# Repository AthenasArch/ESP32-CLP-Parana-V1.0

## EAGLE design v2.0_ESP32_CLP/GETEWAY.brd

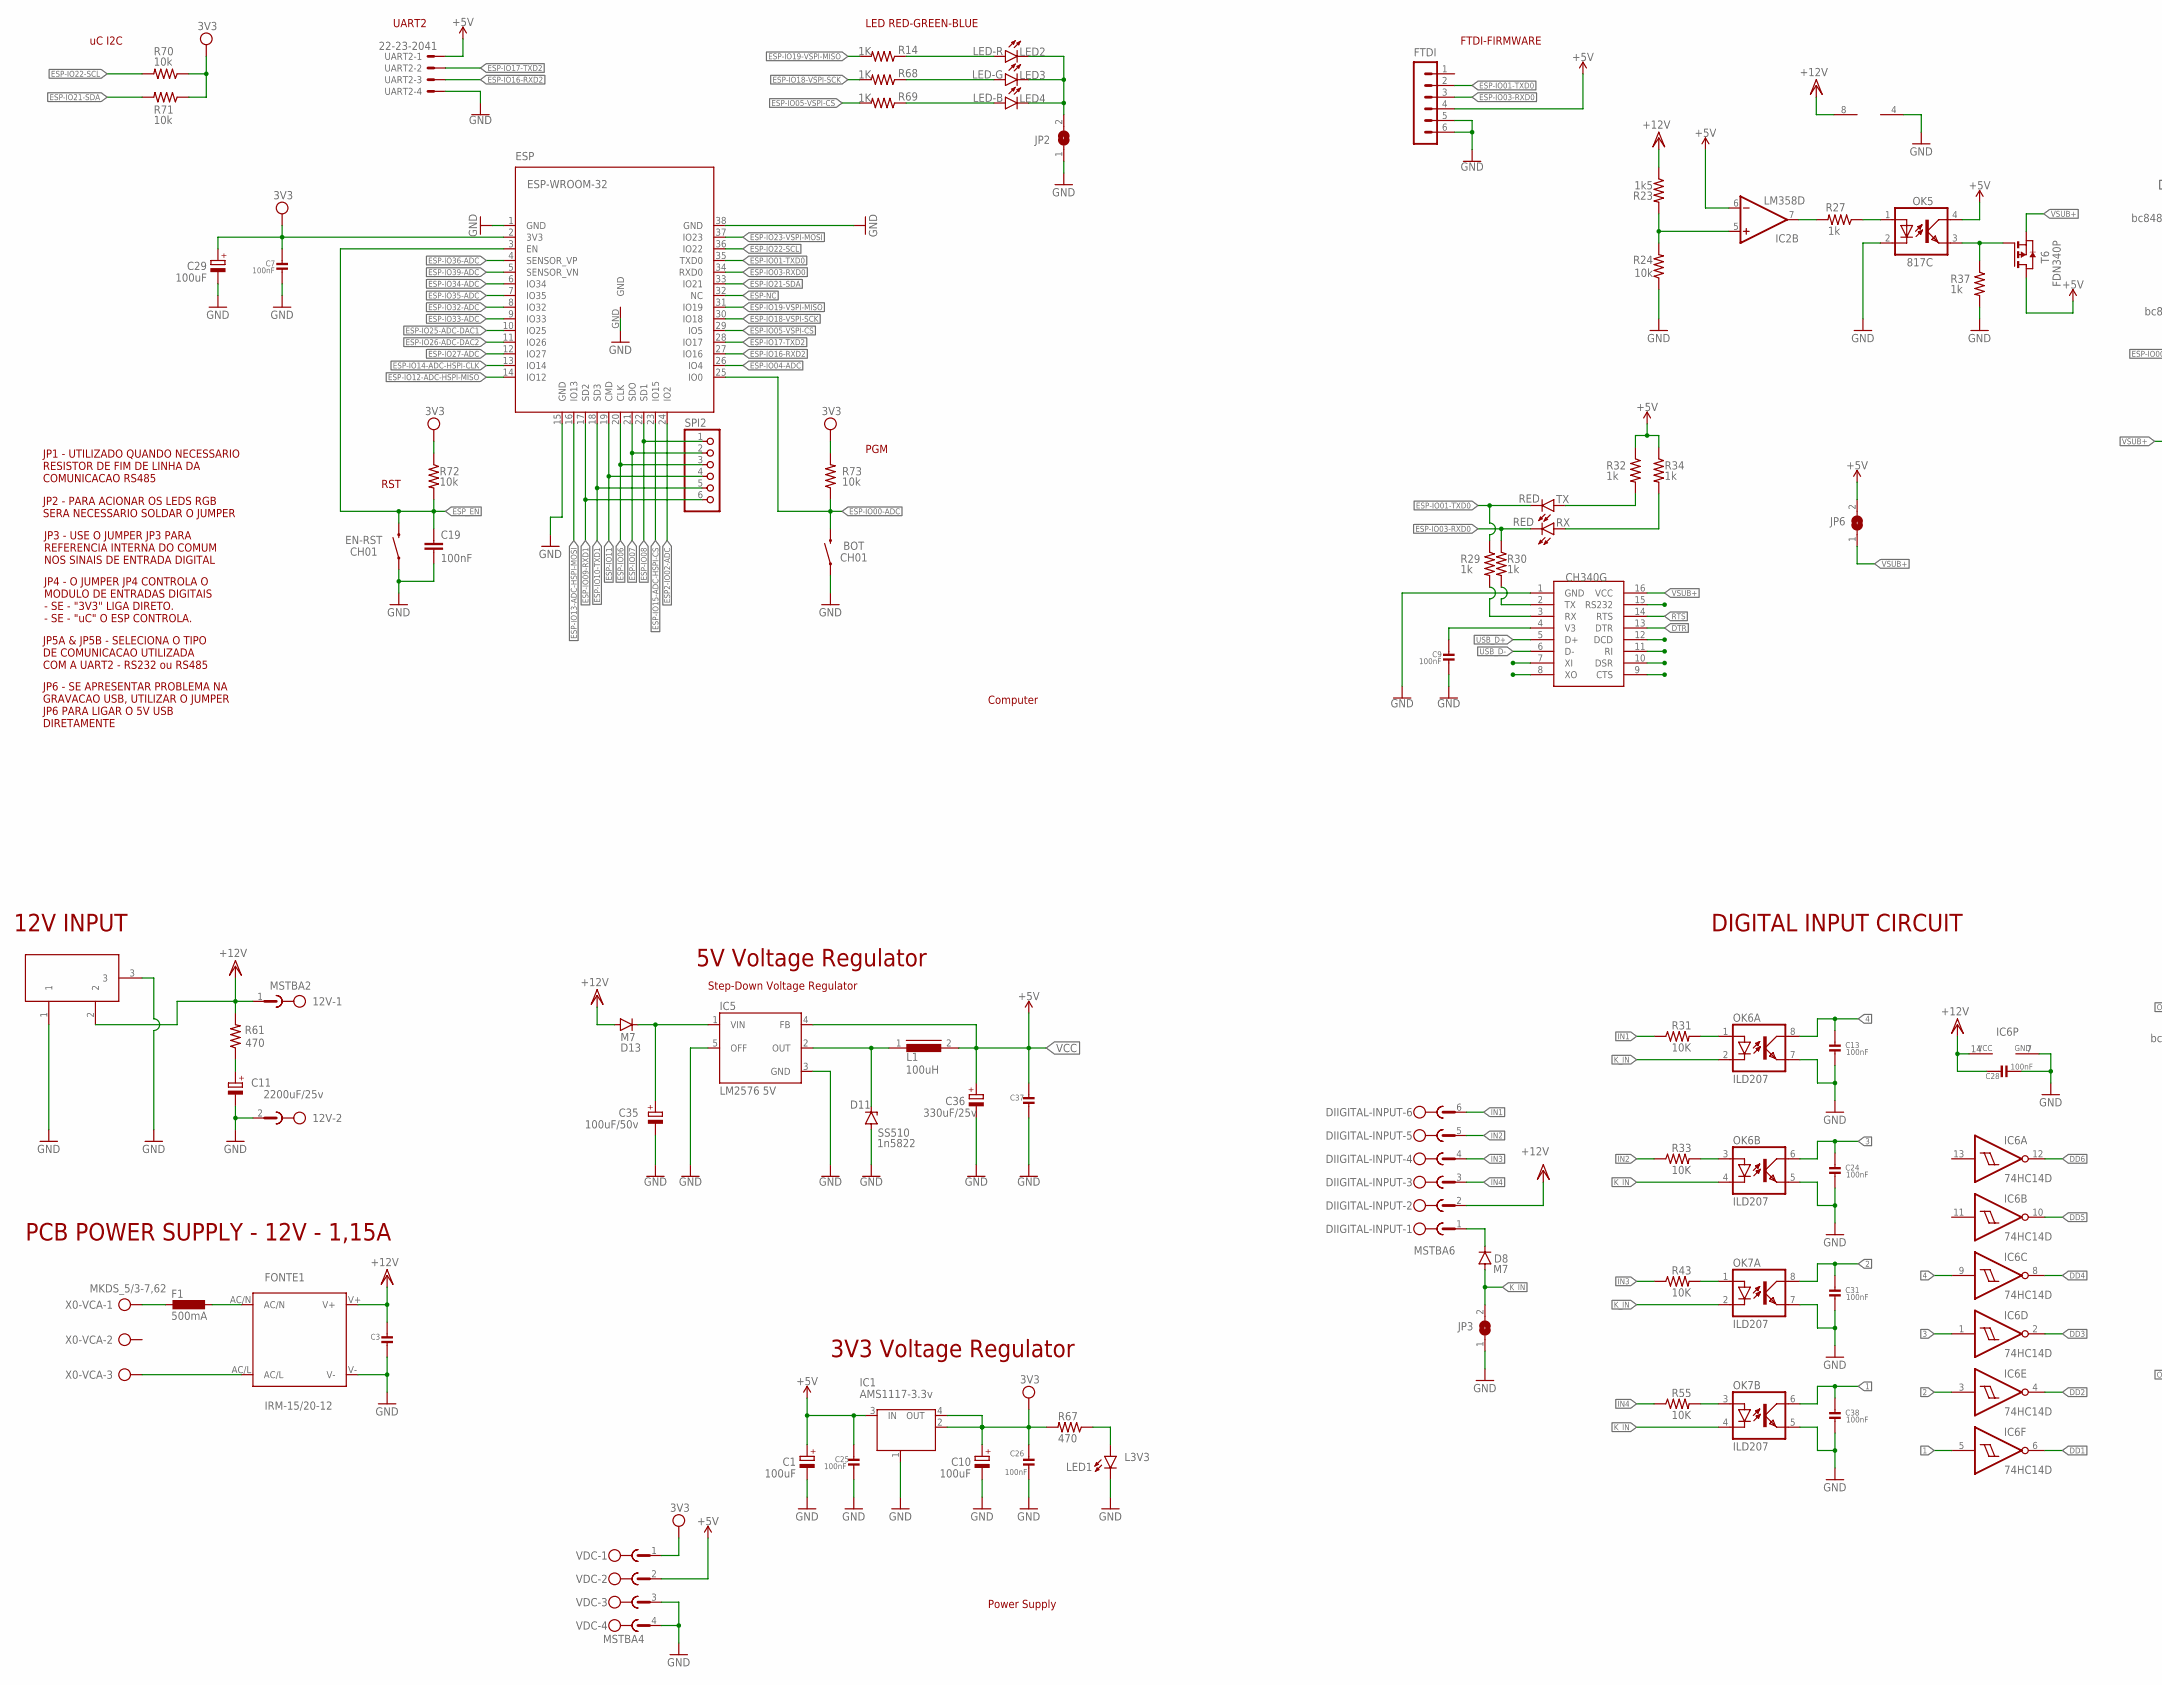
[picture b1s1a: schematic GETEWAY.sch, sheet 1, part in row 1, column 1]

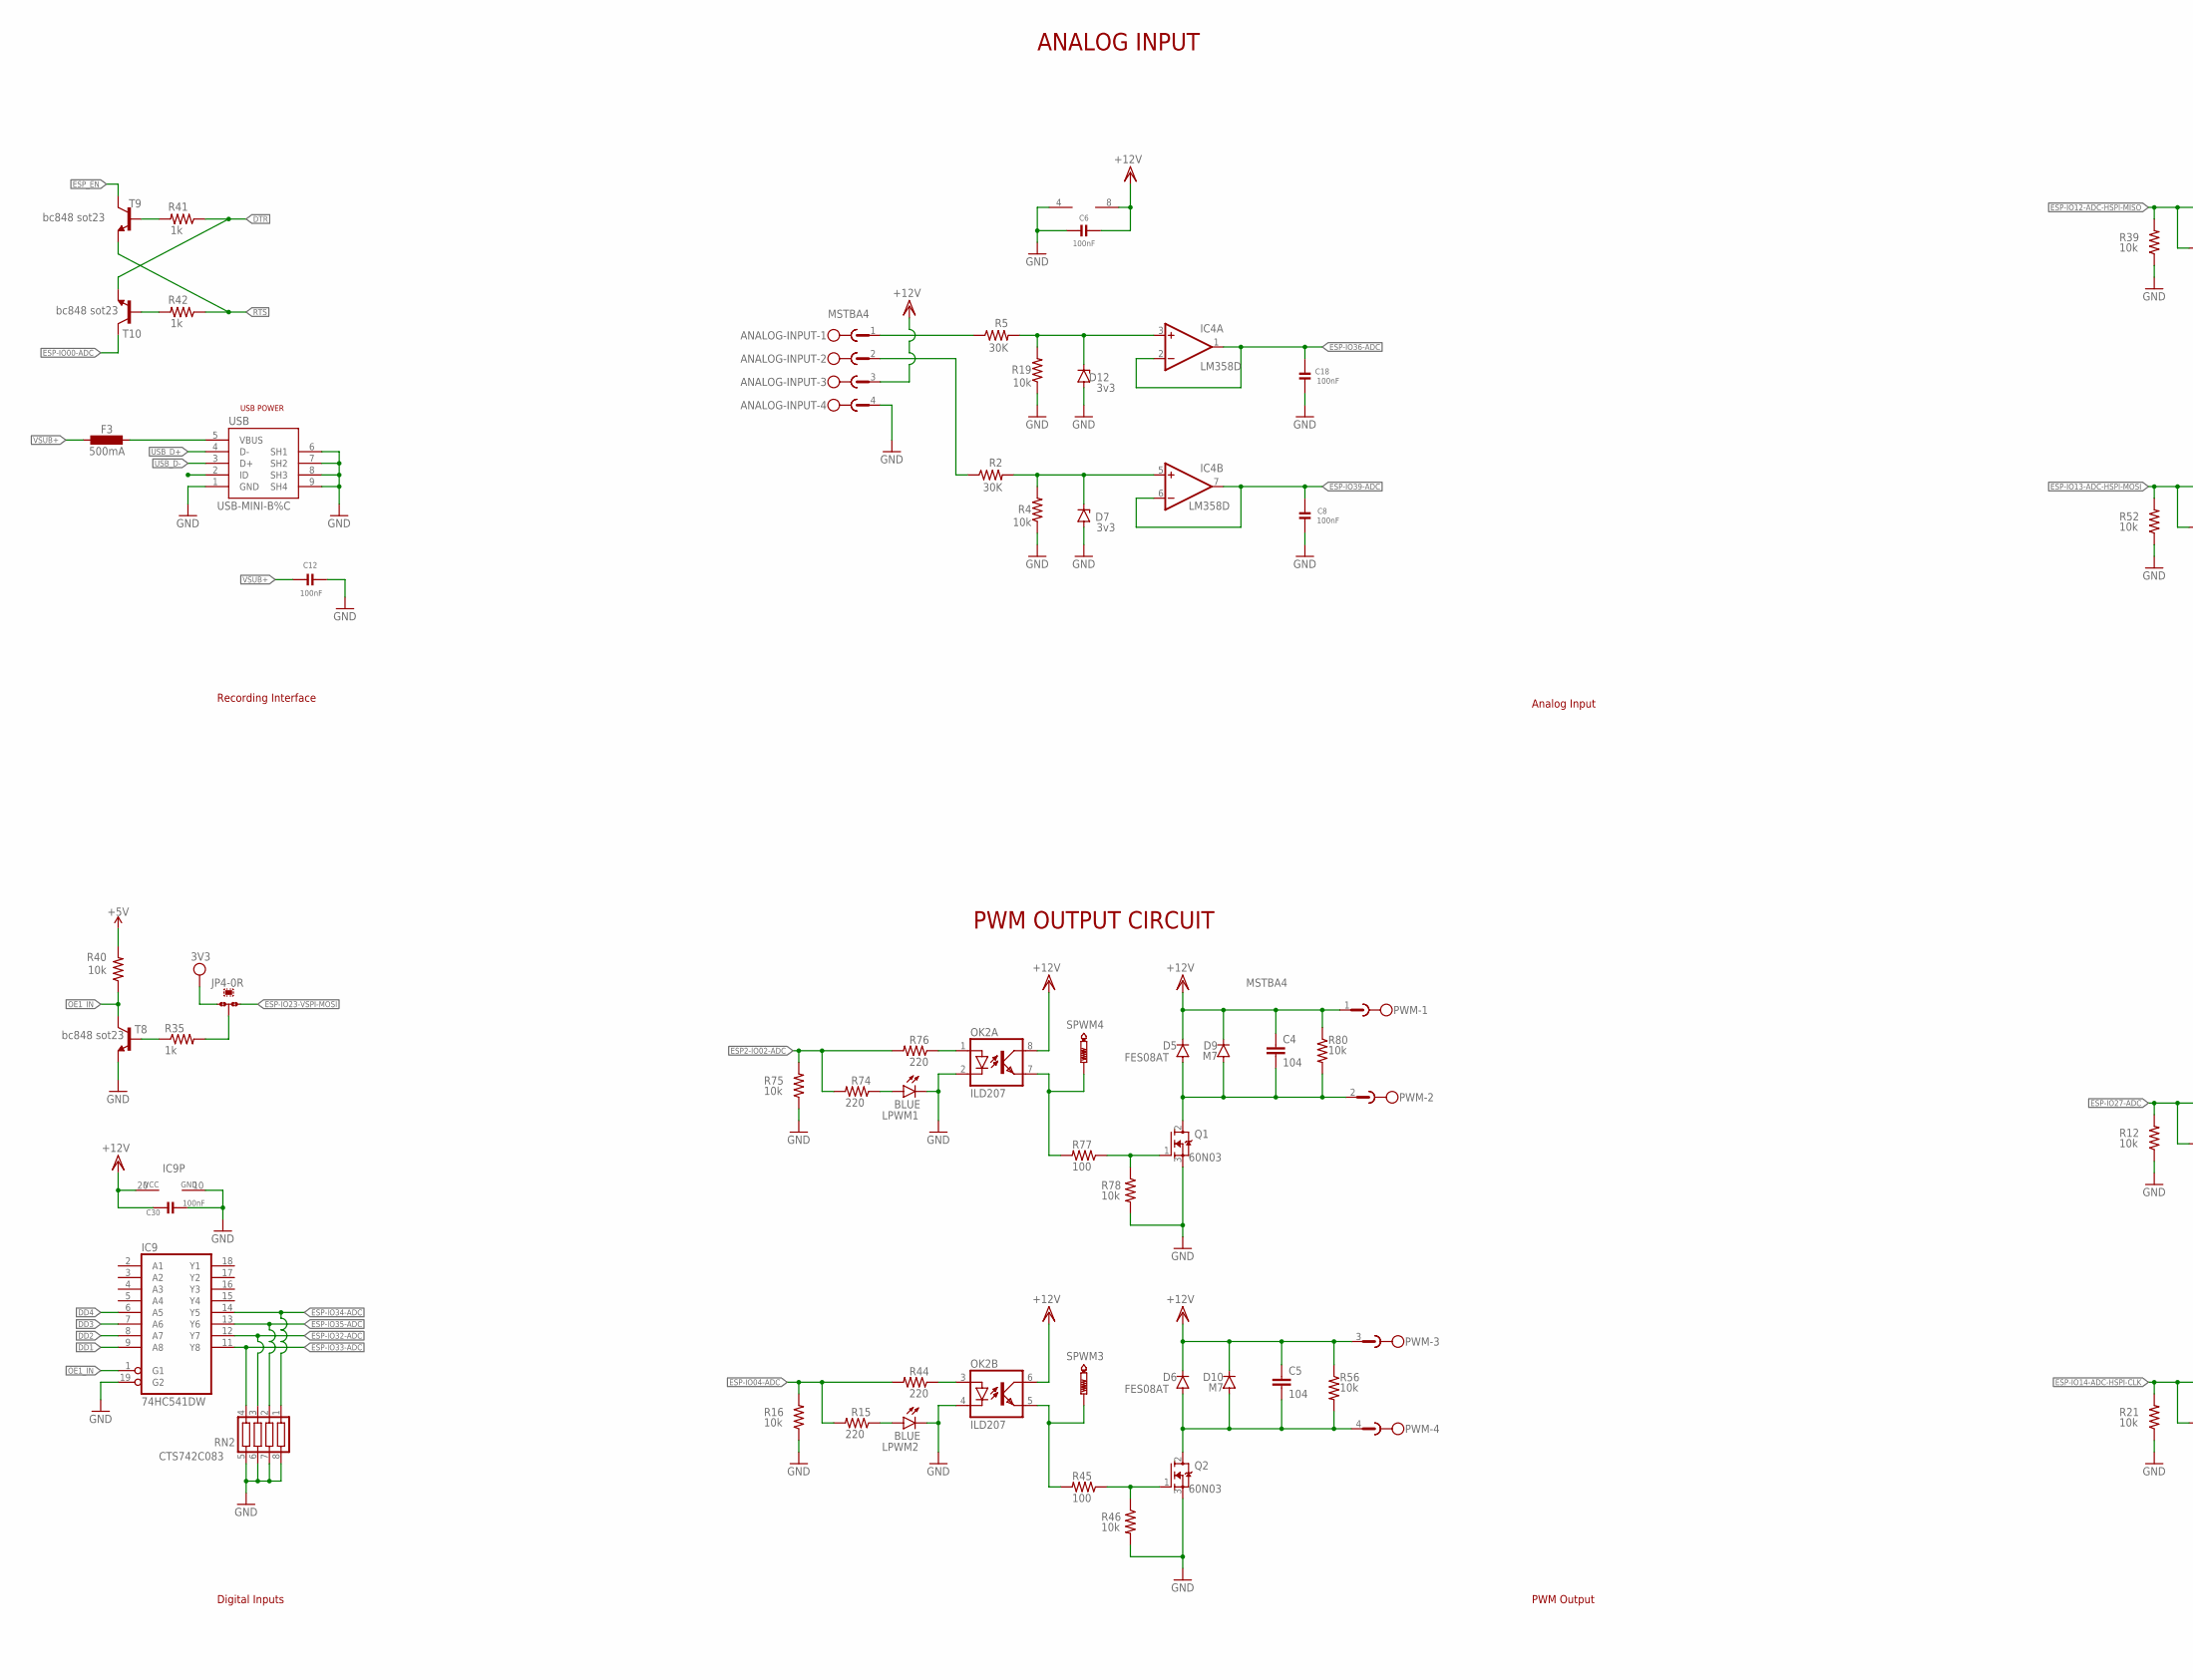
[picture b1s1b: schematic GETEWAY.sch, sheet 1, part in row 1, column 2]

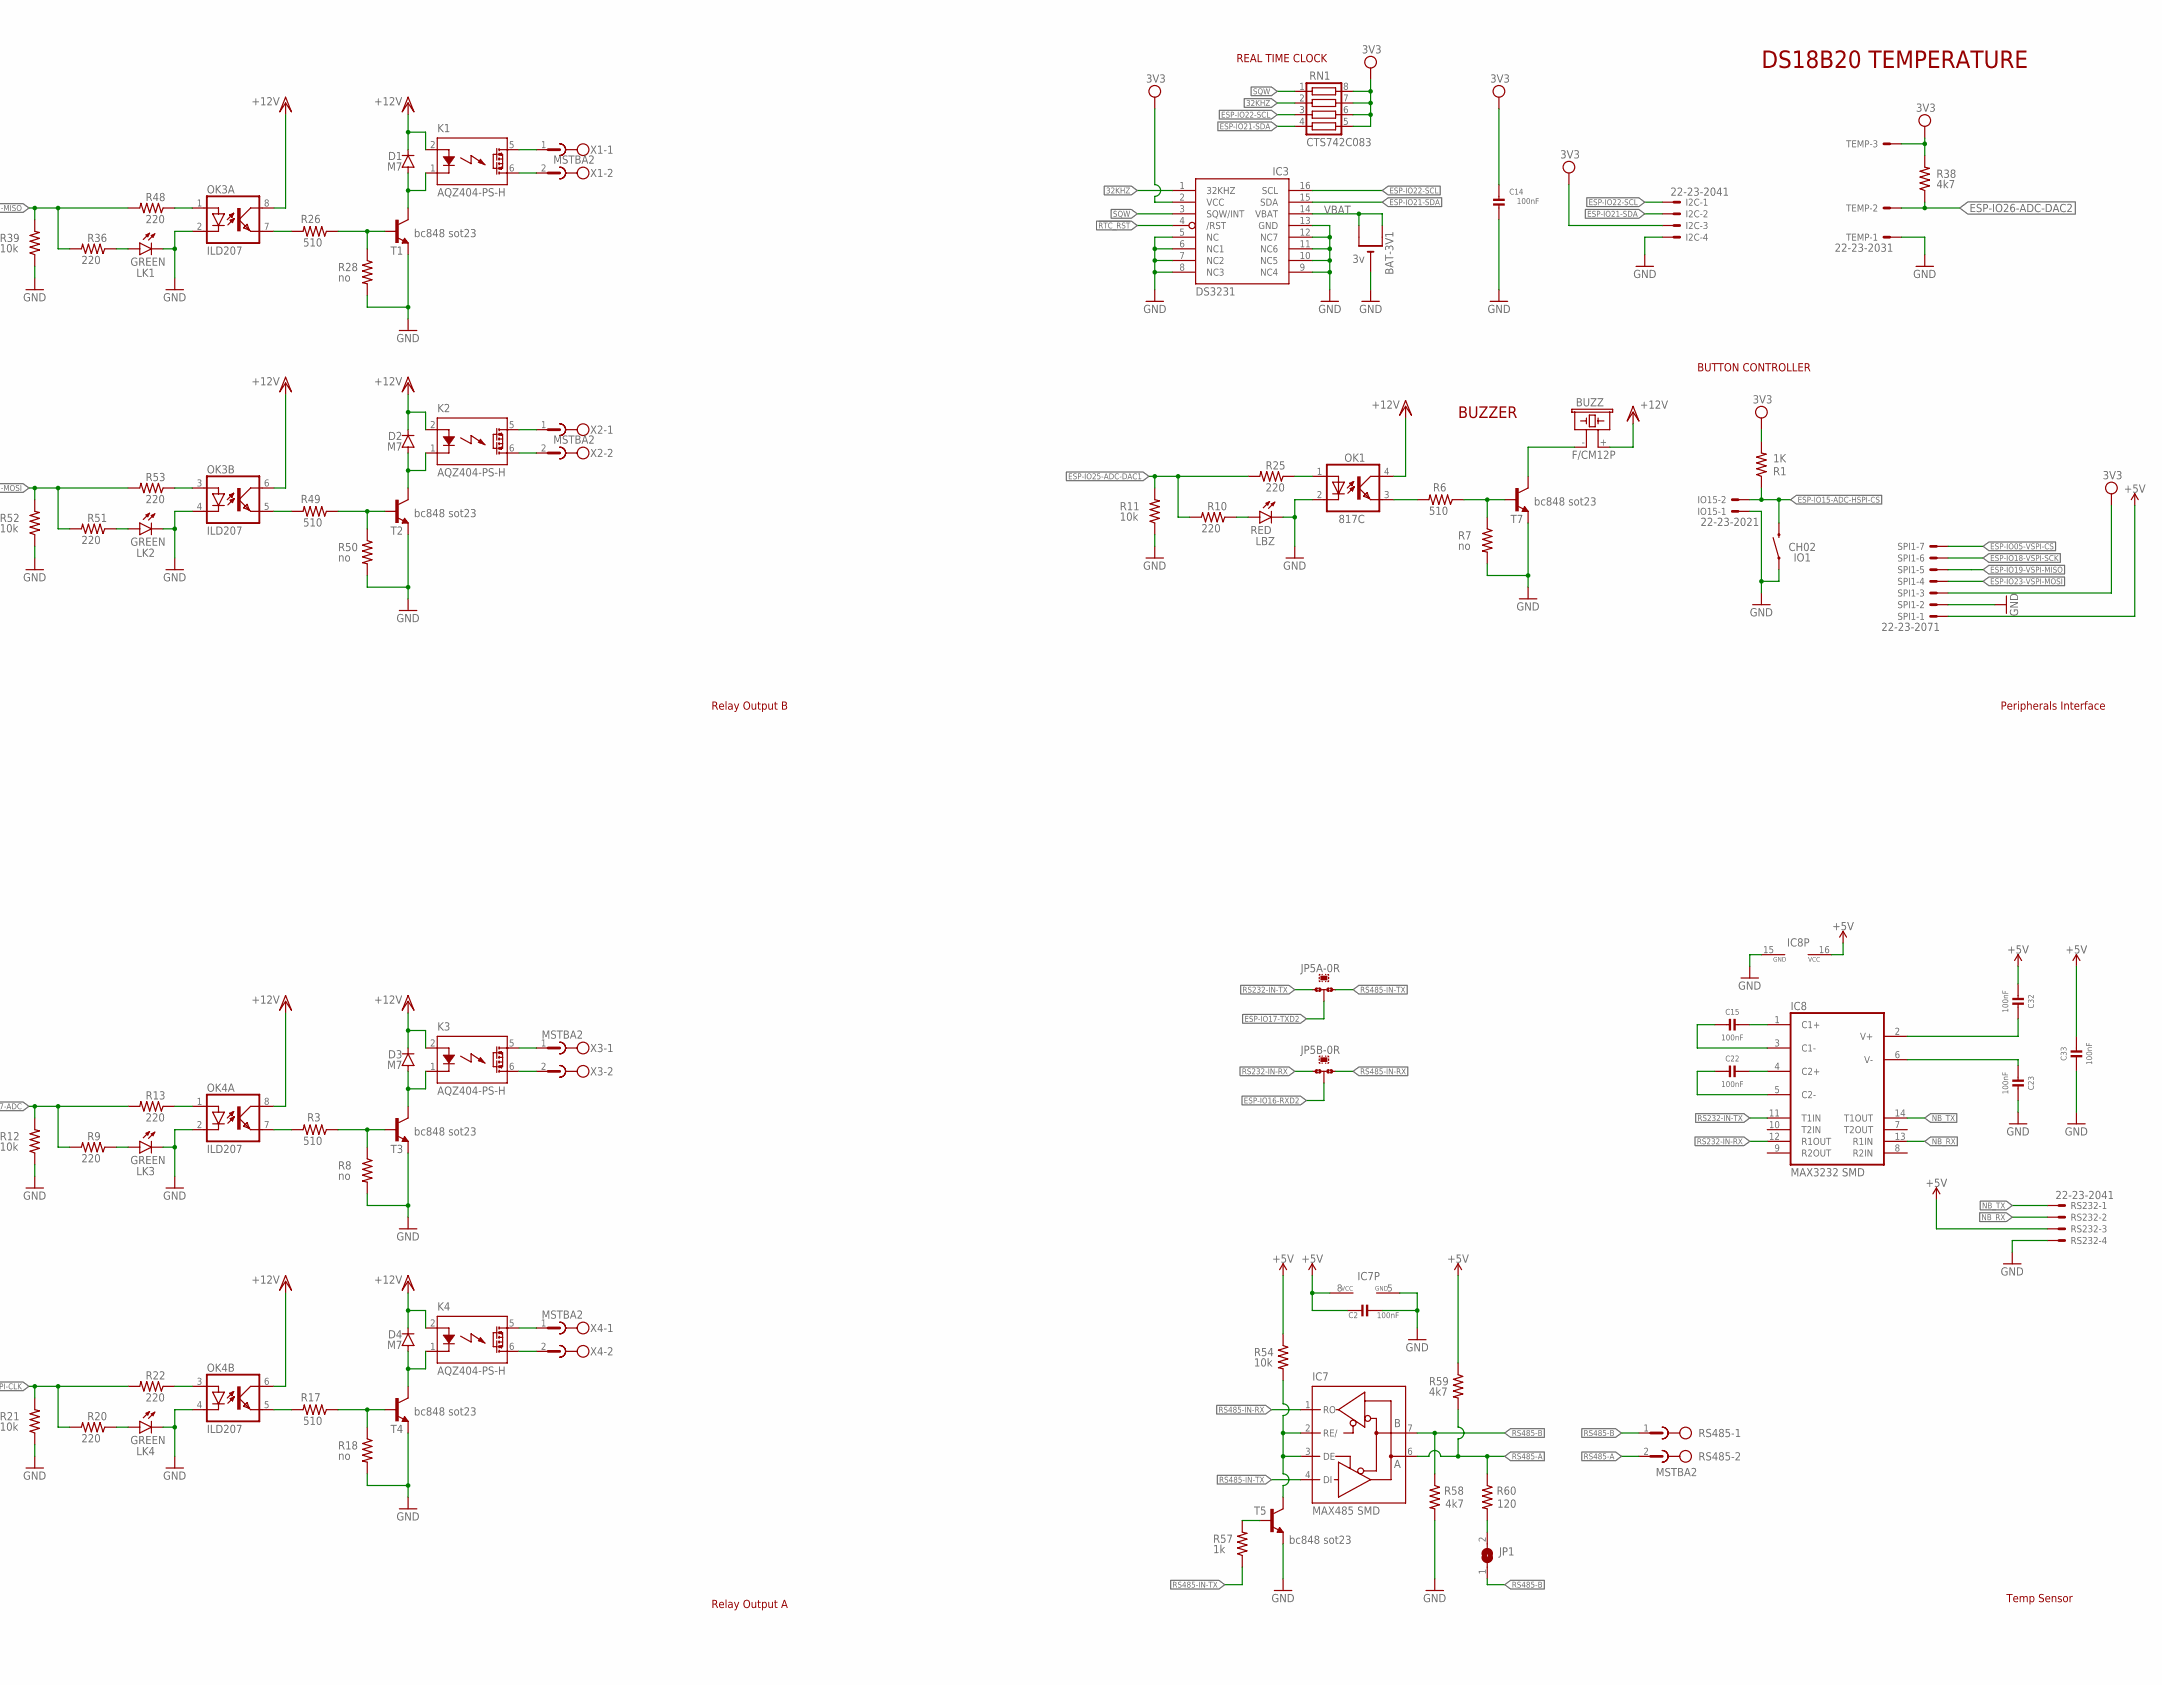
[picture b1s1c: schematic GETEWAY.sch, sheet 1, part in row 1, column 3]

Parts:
7V-15VDC: DC21MMX; DC-21MM
12V: MSTBA2
ANALOG-INPUT: MSTBA4
BAT-3V1: 3v; CR2032-SMD
BOT: CH01; TACTILE_SWITCH_SMD_6.0X3.5MM
BUZZ: F/CM12P
C1, C10, C29: 100uF; E2,5-7
C2, C3, C6, C7, C8, C9, C12, C13, C14, C15, C18, C22, C23, C24, C25, C26, C28, C30, C31, C32, C33, C37, C38: 100nF; 0805-NO
C4, C5: 104; 0805
C11: 2200uF/25v; E5-13
C19: 100nF; C0603
C35: 100uF/50v; E3,5-8
C36: 330uF/25v; E3,5-8
D1, D2, D3, D4, D8, D9, D10, D13: M7; SMB
D5, D6: FES08AT; DO220S
D7, D12: 3v3; SMB
D11: SS510; SMB
DIIGITAL-INPUT: MSTBA6
EN-RST: CH01; TACTILE_SWITCH_SMD_6.0X3.5MM
ESP: ESP-WROOM-32
F1, F3: 500mA; L1812
FONTE1: IRM-15/20-12; IRM_15/20
FTDI: MA06-1
I2C: 22-23-2041
IC1: AMS1117-3.3v; SOT223
IC2, IC4: LM358D; SO08
IC3: DS3231/SO; SO16W
IC5: LM2576 5V; TO263-5
IC6: 74HC14D; SO14
IC7: MAX485 SMD; SO08
IC8: MAX3232 SMD; SO16
IC9: 74HC541DW; SO20W
IO1: CH02; TACTILE_SWITCH_SMD_6.0X3.5MM
IO15: 22-23-2021
JP1, JP2, JP3, JP6: SJ
JP4, JP5A, JP5B: 0R-JUMPA; A0R-JMP
K1, K2, K3, K4: AQZ404-PS-H
L1: 100uH; DR125
L3V3: LED1; CHIPLED_0805
LBZ: RED; CHIPLED_0805
LED-B: LED4; CHIPLED_0805
LED-G: LED3; CHIPLED_0805
LED-R: LED2; CHIPLED_0805
LK1, LK2, LK3, LK4: GREEN; CHIPLED_0805
LPWM1, LPWM2: BLUE; CHIPLED_0805
OK1, OK5: 817C; SMD4-7
OK2, OK3, OK4, OK6, OK7: ILD207; SOIC08
PWM: MSTBA4
Q1, Q2: 60N03; TRANS_AP70T03GH-HF-3TR
R1, R14, R68, R69: 1K; R0805
R2, R5: 30K; R0603
R3, R6, R17, R26, R49: 510; R0603
R4, R11, R12, R16, R19, R21, R24, R39, R40, R46, R52, R54, R56, R70, R71, R72, R73, R75, R78, R80: 10k; R0603
R7, R8, R18, R28, R50: no; R0603
R9, R10, R13, R15, R20, R22, R25, R36, R44, R48, R51, R53, R74, R76: 220; R0603
R23: 1k5; R0603
R27, R29, R30, R32, R34, R35, R37, R41, R42, R57: 1k; R0603
R31, R33, R43, R55: 10K; M1206
R38, R58, R59: 4k7; R0603
R45, R77: 100; R0603
R60: 120; R0603
R61: 470; M1206
R67: 470; R0603
RN1, RN2: CTS742C083
RS232: 22-23-2041
RS485: MSTBA2
RX: RED; CHIPLED_0805
SPI1: 22-23-2071
SPI2: PINHD-1X6; 1X06
SPWM3, SPWM4: PTR1PAD1-17; P1-17
T1, T2, T3, T4, T5, T7, T8, T9, T10: bc848 sot23; SOT23-BEC
T6: FDN340P; SOT-23
TEMP: 22-23-2031
TX: RED; CHIPLED_0805
U2: CH340G; SOIC16
UART2: 22-23-2041
USB: USB-MINI-B%C; USB-MINI-B_2
VDC: MSTBA4
X0-VCA: MKDS_5/3-7,62; MKDS_5/3-762
X1, X2, X3, X4: MSTBA2

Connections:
1: C38.2, IC6.5 (I), OK7.6 (COL)
2: C31.2, IC6.3 (I), OK7.8 (COL)
3: C24.2, IC6.1 (I), OK6.6 (COL)
4: C13.2, IC6.9 (I), OK6.8 (COL)
32KHZ: IC3.1 (32KHZ), RN1.2
!RTC_RST: IC3.4 (/RST)
DD1: IC6.6 (O), IC9.9 (A8)
DD2: IC6.4 (O), IC9.8 (A7)
DD3: IC6.2 (O), IC9.7 (A6)
DD4: IC6.8 (O), IC9.6 (A5)
DD5: IC6.10 (O)
DD6: IC6.12 (O)
DTR: R41.1, T10.E, U2.13 (DTR)
ESP2-IO02-ADC: ESP.24 (IO2), R74.2, R75.2, R76.2
ESP-IO00-ADC: BOT.2, ESP.25 (IO0), R73.1, T10.C
ESP-IO01-TXD0: ESP.35 (TXD0), FTDI.2, R29.1, TX.C
ESP-IO03-RXD0: ESP.34 (RXD0), FTDI.3, R30.1, RX.C
ESP-IO04-ADC: ESP.26 (IO4), R15.2, R16.2, R44.2
ESP-IO05-VSPI-CS: ESP.29 (IO5), R69.2, SPI1.7
ESP-IO06: ESP.20 (CLK), SPI2.3
ESP-IO07: ESP.21 (SDO), SPI2.2
ESP-IO08: ESP.22 (SD1), SPI2.1
ESP-IO09-RXD1: ESP.17 (SD2), SPI2.6
ESP-IO10-TXD1: ESP.18 (SD3), SPI2.5
ESP-IO11: ESP.19 (CMD), SPI2.4
ESP-IO12-ADC-HSPI-MISO: ESP.14 (IO12), R36.2, R39.2, R48.2
ESP-IO13-ADC-HSPI-MOSI: ESP.16 (IO13), R51.2, R52.2, R53.2
ESP-IO14-ADC-HSPI-CLK: ESP.13 (IO14), R20.2, R21.2, R22.2
ESP-IO15-ADC-HSPI-CS: ESP.23 (IO15), IO1.2, IO15.2, R1.1
ESP-IO16-RXD2: ESP.27 (IO16), JP5B.2, UART2.3
ESP-IO17-TXD2: ESP.28 (IO17), JP5A.2, UART2.2
ESP-IO18-VSPI-SCK: ESP.30 (IO18), R68.2, SPI1.6
ESP-IO19-VSPI-MISO: ESP.31 (IO19), R14.2, SPI1.5
ESP-IO21-SDA: ESP.33 (IO21), I2C.2, IC3.15 (SDA), R71.2, RN1.4
ESP-IO22-SCL: ESP.36 (IO22), I2C.1, IC3.16 (SCL), R70.2, RN1.3
ESP-IO23-VSPI-MOSI: ESP.37 (IO23), JP4.1, SPI1.4
ESP-IO25-ADC-DAC1: ESP.10 (IO25), R10.2, R11.2, R25.2
ESP-IO26-ADC-DAC2: ESP.11 (IO26), R38.1, TEMP.2
ESP-IO27-ADC: ESP.12 (IO27), R9.2, R12.2, R13.2
ESP-IO32-ADC: ESP.8 (IO32), IC9.12 (Y7), RN2.3
ESP-IO33-ADC: ESP.9 (IO33), IC9.11 (Y8), RN2.4
ESP-IO34-ADC: ESP.6 (IO34), IC9.14 (Y5), RN2.1
ESP-IO35-ADC: ESP.7 (IO35), IC9.13 (Y6), RN2.2
ESP-IO36-ADC: C18.2, ESP.4 (SENSOR_VP), IC4.1 (OUT), IC4.2 (-IN)
ESP-IO36-ADC1: IC2.7 (OUT), R27.2
ESP-IO39-ADC: C8.2, ESP.5 (SENSOR_VN), IC4.6 (-IN), IC4.7 (OUT)
ESP-NC: ESP.32 (NC)
ESP_EN: C19.1, EN-RST.2, ESP.3 (EN), R72.2, T9.C
GND: 7V-15VDC.1, 7V-15VDC.3, 12V.2, ANALOG-INPUT.4, BAT-3V1.-, BOT.1, C1.-, C2.1, C3.1, C6.2, C7.1, C8.1, C9.1, C10.-, C11.-, C12.1, C13.1, C14.1, C18.1, C19.2, C23.1, C24.1, C25.1, C26.1, C28.1, C29.-, C30.1, C31.1, C33.2, C35.-, C36.-, C37.1, C38.1, D7.A, D11.A, D12.A, EN-RST.1, ESP.1 (GND), ESP.15 (GND), ESP.38 (GND), ESP.GND, FONTE1.V-, FTDI.5, FTDI.6, I2C.4, IC1.1 (GND/ADJ), IC2.4 (V-), IC3.5 (NC), IC3.6 (NC1), IC3.7 (NC2), IC3.8 (NC3), IC3.9 (NC4), IC3.10 (NC5), IC3.11 (NC6), IC3.12 (NC7), IC3.13 (GND), IC4.4 (V-), IC5.3 (GND), IC5.5 (OFF), IC6.7 (GND), IC7.5 (GND), IC8.15 (GND), IC9.10 (GND), IC9.19 (G2), IO1.1, IO15.1, JP2.1, JP3.1, L3V3.C, LBZ.C, LK1.C, LK2.C, LK3.C, LK4.C, LPWM1.C, LPWM2.C, OK1.2 (C), OK2.2 (C), OK2.4 (C), OK3.2 (C), OK3.4 (C), OK4.2 (C), OK4.4 (C), OK5.2 (C), OK6.5 (EMIT), OK6.7 (EMIT), OK7.5 (EMIT), OK7.7 (EMIT), Q1.3 (S), Q2.3 (S), R4.1, R7.2, R8.2, R11.1, R12.1, R16.1, R18.2, R19.1, R21.1, R24.1, R28.2, R37.2, R39.1, R46.2, R50.2, R52.1, R58.2, R75.1, R78.2, RN2.5, RN2.6, RN2.7, RN2.8, RS232.4, SPI1.2, T1.E, T2.E, T3.E, T4.E, T5.E, T7.E, T8.E, TEMP.1, U2.1 (GND), UART2.4, USB.1 (GND), USB.6 (SH1), USB.7 (SH2), USB.8 (SH3), USB.9 (SH4), VDC.3, VDC.4
IN1: DIIGITAL-INPUT.6, R31.1
IN2: DIIGITAL-INPUT.5, R33.1
IN3: DIIGITAL-INPUT.4, R43.1
IN4: DIIGITAL-INPUT.3, R55.1
K_IN: D8.A, JP3.2, OK6.2 (C), OK6.4 (C), OK7.2 (C), OK7.4 (C)
unnamed: D1.A, K1.1 (K), T1.C
unnamed: R26.1, R28.1, T1.B
unnamed: OK3.7 (EMIT), R26.2
unnamed: C15.1, IC8.1 (C1+)
unnamed: C15.2, IC8.3 (C1-)
unnamed: C22.1, IC8.4 (C2+)
unnamed: C22.2, IC8.5 (C2-)
unnamed: C23.2, IC8.6 (V-)
unnamed: C32.1, IC8.2 (V+)
unnamed: BUZZ.- (2), T7.C
unnamed: R6.1, R7.1, T7.B
unnamed: K1.5 (DS1), X1.1
unnamed: K1.6 (DS2), X1.2
unnamed: K2.5 (DS1), X2.1
unnamed: ANALOG-INPUT.1, R5.1
unnamed: ANALOG-INPUT.2, R2.1
unnamed: D3.A, K3.1 (K), T3.C
unnamed: OK3.1 (A), R48.1
unnamed: D7.C, IC4.5 (+IN), R2.2, R4.2
unnamed: OK1.3 (EMIT), R6.2
unnamed: OK1.1 (A), R25.1
unnamed: R3.1, R8.1, T3.B
unnamed: LBZ.A, R10.1
unnamed: LK1.A, R36.1
unnamed: OK4.7 (EMIT), R3.2
unnamed: LED-R.A, R14.1
unnamed: R35.1, T8.B
unnamed: D2.A, K2.1 (K), T2.C
unnamed: K3.5 (DS1), X3.1
unnamed: K3.6 (DS2), X3.2
unnamed: K4.5 (DS1), X4.1
unnamed: R49.1, R50.1, T2.B
unnamed: OK6.1 (A), R31.2
unnamed: OK6.3 (A), R33.2
unnamed: OK4.1 (A), R13.1
unnamed: LK3.A, R9.1
unnamed: LED-G.A, R68.1
unnamed: LED-B.A, R69.1
unnamed: D4.A, K4.1 (K), T4.C
unnamed: R17.1, R18.1, T4.B
unnamed: OK3.5 (EMIT), R49.2
unnamed: OK2.3 (A), R44.1
unnamed: JP2.2, LED-B.C, LED-G.C, LED-R.C
unnamed: C9.2, U2.4 (V3)
unnamed: R29.2, U2.3 (RX)
unnamed: R30.2, U2.2 (TX)
unnamed: R34.2, RX.A
unnamed: OK7.1 (A), R43.2
unnamed: LPWM2.A, R15.1
unnamed: OK7.3 (A), R55.2
unnamed: OK2.5 (EMIT), R45.2, SPWM3.TP
unnamed: D8.C, DIIGITAL-INPUT.1
unnamed: JP4.2, R35.2
unnamed: D12.C, IC4.3 (+IN), R5.2, R19.2
unnamed: K2.6 (DS2), X2.2
unnamed: F1.2, X0-VCA.1
unnamed: F1.1, FONTE1.AC/N
unnamed: OK3.3 (A), R53.1
unnamed: LK2.A, R51.1
unnamed: IC2.5 (+IN), R23.2, R24.2
unnamed: K4.6 (DS2), X4.2
unnamed: OK5.1 (A), R27.1
unnamed: Q2.1 (G), R45.1, R46.1
unnamed: C5.2, D6.A, D10.A, PWM.4, Q2.2 (D), R56.2
unnamed: OK2.1 (A), R76.1
unnamed: LPWM1.A, R74.1
unnamed: OK2.7 (EMIT), R77.2, SPWM4.TP
unnamed: Q1.1 (G), R77.1, R78.1
unnamed: OK5.3 (EMIT), R37.1, T6.3 (G)
unnamed: F3.1, USB.5 (VBUS)
unnamed: FONTE1.AC/L, X0-VCA.3
unnamed: C4.2, D5.A, D9.A, PWM.2, Q1.2 (D), R80.2
unnamed: R57.2, T5.B
unnamed: IC7.2 (RE/), IC7.3 (DE), R54.2, T5.C
unnamed: L3V3.A, R67.1
unnamed: C11.+, R61.1
unnamed: JP1.2, R60.2
unnamed: D11.C, IC5.2 (OUT), L1.1
unnamed: C35.+, D13.C, IC5.1 (VIN)
unnamed: R32.2, TX.A
unnamed: R42.2, T10.B
unnamed: OK4.5 (EMIT), R17.2
unnamed: OK4.3 (A), R22.1
unnamed: R41.2, T9.B
unnamed: LK4.A, R20.1
NB_RX: IC8.13 (R1IN), RS232.2
NB_TX: IC8.14 (T1OUT), RS232.1
OE1_IN: IC9.1 (G1), R40.1, T8.C
RS232-IN-RX: IC8.12 (R1OUT), JP5B.3
RS232-IN-TX: IC8.11 (T1IN), JP5A.3
RS485-A: IC7.6 (A), R59.2, R60.1, RS485.2
RS485-B: IC7.7 (B), JP1.1, R58.1, RS485.1
RS485-IN-RX: IC7.1 (RO), JP5B.1
RS485-IN-TX: IC7.4 (DI), JP5A.1, R57.1
RTS: R42.1, T9.E, U2.14 (RTS)
SQW: IC3.3 (SQW/INT), RN1.1
USB_D+: U2.5 (D+), USB.4 (D-)
USB_D-: U2.6 (D-), USB.3 (D+)
VBAT: BAT-3V1.+$1 (+), BAT-3V1.+$2 (+1), IC3.14 (VBAT)
VCC: C1.+, C2.2, C25.2, C32.2, C33.1, C36.+, C37.2, FTDI.4, IC1.3 (IN), IC2.6 (-IN), IC5.4 (FB), IC7.8 (VCC), IC8.16 (VCC), JP6.2, L1.2, OK5.4 (COL), R32.1, R34.1, R40.2, R54.1, R59.1, RS232.3, SPI1.1, T6.1 (D), UART2.1, VDC.2
VDD: 7V-15VDC.2, 12V.1, ANALOG-INPUT.3, BUZZ.+ (1), C3.2, C4.1, C5.1, C6.1, C28.2, C30.2, D1.C, D2.C, D3.C, D4.C, D5.C, D6.C, D9.C, D10.C, D13.A, DIIGITAL-INPUT.2, FONTE1.V+, IC2.8 (V+), IC4.8 (V+), IC6.14 (VCC), IC9.20 (VCC), K1.2 (A), K2.2 (A), K3.2 (A), K4.2 (A), OK1.4 (COL), OK2.6 (COL), OK2.8 (COL), OK3.6 (COL), OK3.8 (COL), OK4.6 (COL), OK4.8 (COL), PWM.1, PWM.3, R23.1, R56.1, R61.2, R80.1
VEE: C7.2, C10.+, C14.2, C26.2, C29.+, ESP.2 (3V3), I2C.3, IC1.2 (OUT), IC1.4 (OUT), IC3.2 (VCC), JP4.3, R1.2, R38.2, R67.2, R70.1, R71.1, R72.1, R73.2, RN1.5, RN1.6, RN1.7, RN1.8, SPI1.3, TEMP.3, VDC.1
VSUB+: C12.2, F3.2, JP6.1, T6.2 (S), U2.16 (VCC)

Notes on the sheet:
3V3 Voltage Regulator
5V Voltage Regulator
12V INPUT
PCB POWER SUPPLY - 12V - 1,15A
1n5822
Step-Down Voltage Regulator
Power Supply
uC I2C
PGM
RST
Computer
FTDI-FIRMWARE
USB POWER
Recording Interface
DIGITAL INPUT CIRCUIT
JP3 - USE O JUMPER JP3 PARA REFERENCIA INTERNA DO COMUM NOS SINAIS DE ENTRADA DIGITAL
Digital Inputs
ANALOG INPUT
Analog Input
PWM OUTPUT CIRCUIT
PWM Output
Relay Output A
Relay Output B
BUZZER
REAL TIME CLOCK
BUTTON CONTROLLER
Peripherals Interface
DS18B20 TEMPERATURE
Temp Sensor
JP2 - PARA ACIONAR OS LEDS RGB SERA NECESSARIO SOLDAR O JUMPER
JP4 - O JUMPER JP4 CONTROLA O MODULO DE ENTRADAS DIGITAIS - SE - "3V3" LIGA DIRETO. - SE - "uC" O ESP CONTROLA.
UART2
LED RED-GREEN-BLUE
JP6 - SE APRESENTAR PROBLEMA NA GRAVACAO USB, UTILIZAR O JUMPER JP6 PARA LIGAR O 5V USB DIRETAMENTE
JP1 - UTILIZADO QUANDO NECESSARIO RESISTOR DE FIM DE LINHA DA COMUNICACAO RS485
JP5A & JP5B - SELECIONA O TIPO DE COMUNICACAO UTILIZADA COM A UART2 - RS232 ou RS485

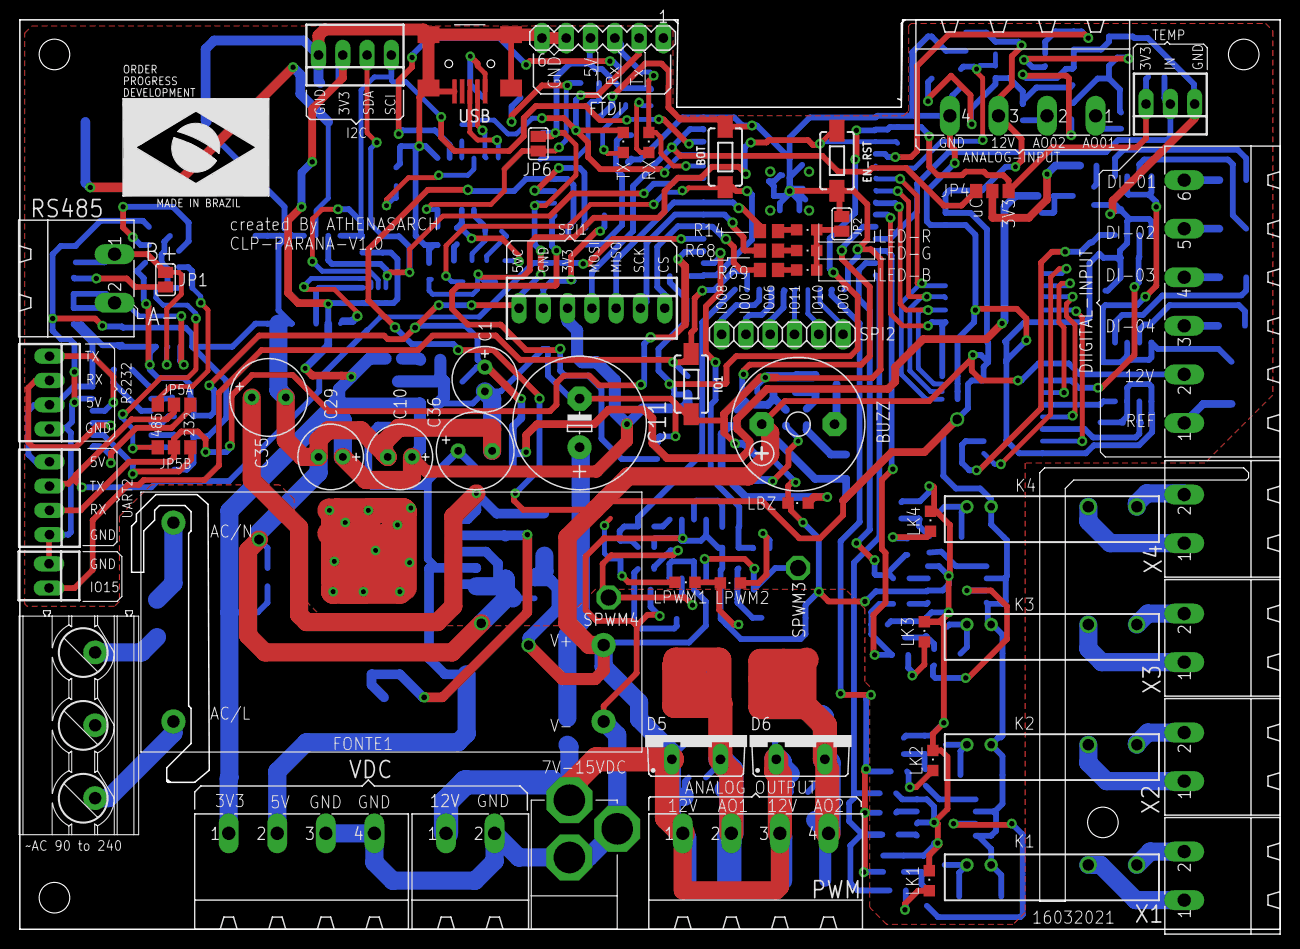
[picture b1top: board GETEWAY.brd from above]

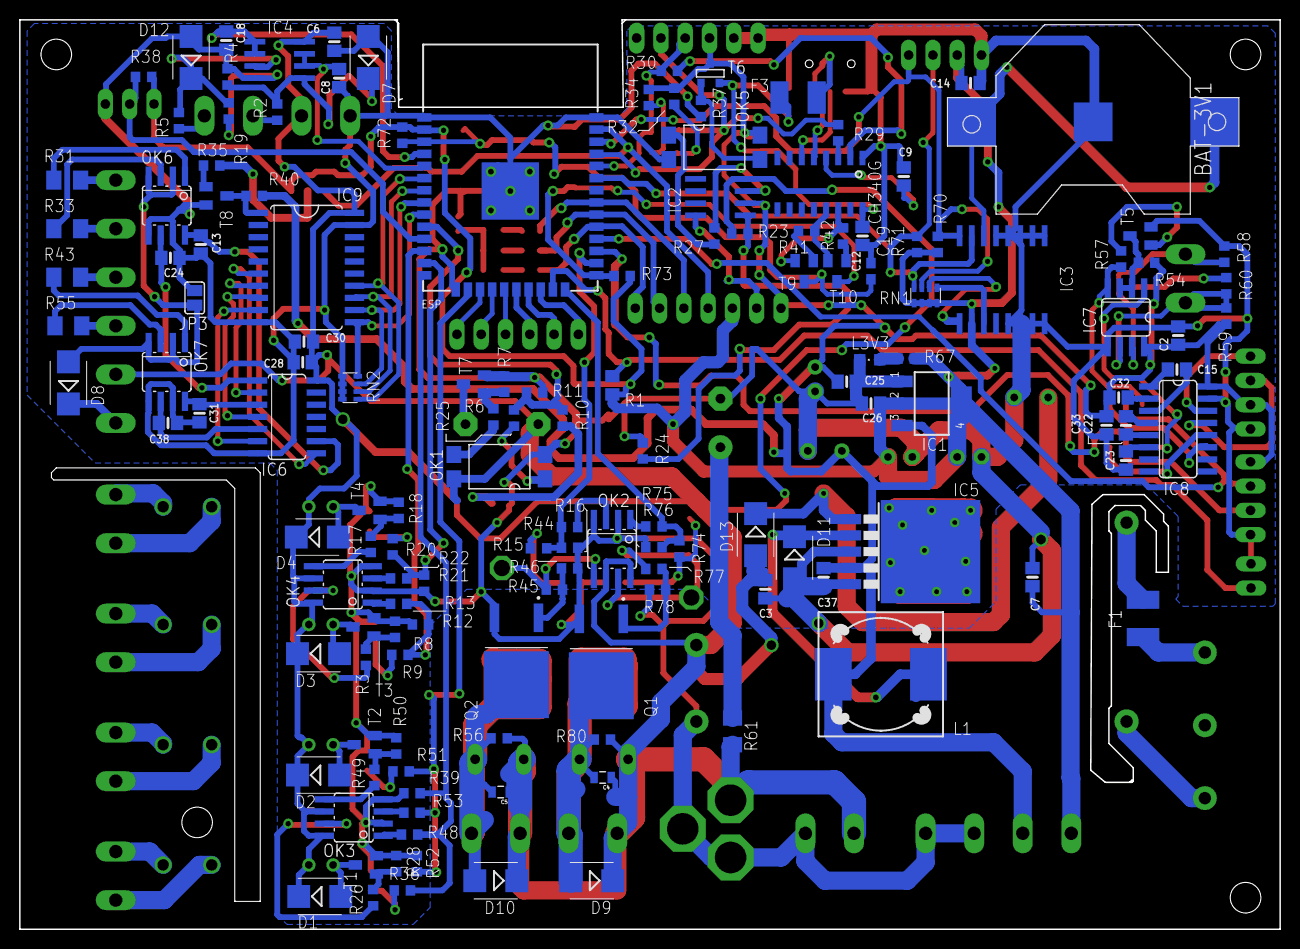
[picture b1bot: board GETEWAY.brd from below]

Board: 2 copper layers, 131.8 x 95.1 mm, 206 parts (145 on the bottom side), 153 nets.

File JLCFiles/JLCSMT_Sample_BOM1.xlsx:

Comment | Designator | Footprint | LCSC Part #（optional）
1K | JP3,R1 | R0805
1k | R27,R29,R30,R32,R34,R35,R37,R41,R42,R57 | R0603
1k5 | R23 | R0603
3v | BAT-3V1 | CR2032-SMD
3v3 | D7,D12 | SMB
4k7 | R38,R58,R59 | R0603
10K | R31,R33,R43,R55 | M1206
10k | R4,R11,R12,R16,R19,R21,R24,R39,R40,R46,R52,R54,R56,R70,R71,R72,R73,R75,R78,R80 | R0603
30K | R2,R5 | R0603
74HC14D | IC6 | SO14
74HC541DW | IC9 | SO20W
100 | R45,R77 | R0603
100nF | C2,C3,C6,C8,C9,C12,C13,C14,C15,C18 | 0805-NO
100nF | C19 | C0603
100nF | C22,C23,C24,C25,C26 | 0805-NO
100nF | C27 | 805
100nF | C28,C30,C31,C32,C33,C37,C38 | 0805-NO
100uH | L1 | DR125
104 | C4,C5 | 805
120 | R60 | R0603
220 | R9,R10,R13,R15,R20,R22,R25,R36,R44,R48,R51,R53,R74,R76 | R0603
470 | R61 | M1206
470 | R67 | R0603
500mA | F1,F3 | L1812
510 | R3,R6,R17,R26,R49 | R0603
817C | OK1,OK5 | SMD4-7
AP70T03GH-HF-3TR | Q1,Q2 | TRANS_AP70T03GH-HF-3TR
CH340G | U2 | SOIC16
CTS742C083 | RN1,RN2 | CTS742C083
DS3231/SO | IC3 | SO16W
ESP-WROOM-32 | ESP | ESP-WROOM-32
FDN340P | T6 | SOT-23
ILD207 | OK2,OK3,OK4,OK6,OK7 | SOIC08
LED1 | L3V3 | CHIPLED_0805
LM358D | IC2,IC4 | SO08
LM2576,5V | IC5 | TO263-5
M7 | D1,D2,D3,D4,D8,D9,D10,D13 | SMB
MAX485,SMD | IC7 | SO08
MAX3232,SMD | IC8 | SO16
NCP1117,3v3, | IC1 | SOT223
SS510 | D11 | SMB
bc848,sot23 | T1,T2,T3,T4,T5,T7,T8,T9,T10 | SOT23-BEC
no | R7,R8,R18,R28,R50 | R0603

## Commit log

2022-11-21 V1.0-CLP Parana - ESP32
    - Primeiro upload do hardware.
    Lembrando que placa precisa de manutenção.

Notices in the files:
parts and their libraries:
SparkFun-Switches: Licensing: Creative Commons ShareAlike 4.0 International - https://creativecommons.org/licenses/by-sa/4.0
microbuilder: This work is placed in the public domain, and may be freely used for commercial and non-commercial work with the following conditions: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
